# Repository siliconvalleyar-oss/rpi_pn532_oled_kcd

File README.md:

# NFC RPi Module

KiCad schematic for an NFC module combining a Raspberry Pi Zero 2W, PN532 NFC reader, and OLED display.

## Project Structure

```
nfc_rpi.kicad_sch          Root schematic
├── nfc.kicad_sch          NFC module (page 2)
│   ├── raspberry_pn532.kicad_sch   Raspberry Pi connector (page 4)
│   ├── pn532.kicad_sch             PN532 NFC controller
│   └── ...
└── ...
```

## Components

- **Raspberry Pi Zero 2W** - Main controller
- **PN532** - NFC/RFID reader/writer (SPI interface)
- **OLED Display** - Status display (I2C interface)

## Hierarchical Pin Mapping

### Raspberry Pi Sheet (J1)

| Pin | Function | Interface |
|-----|----------|-----------|
| SDA | I2C Data | OLED |
| SCL | I2C Clock | OLED |
| GPIO5 | General Purpose | - |
| GPIO6 | General Purpose | - |
| MISO | SPI Data In | PN532 |
| SCK | SPI Clock | PN532 |
| 5V | Power Supply | - |
| GND | Ground | - |

## Notes

- Hierarchical pins connect J1's GPIO pins to the parent schematic
- Global labels (SCL_OLED_RPI, SDA_OLED_RPI) handle I2C routing
- Power distribution uses hierarchical pins for 5V and GND

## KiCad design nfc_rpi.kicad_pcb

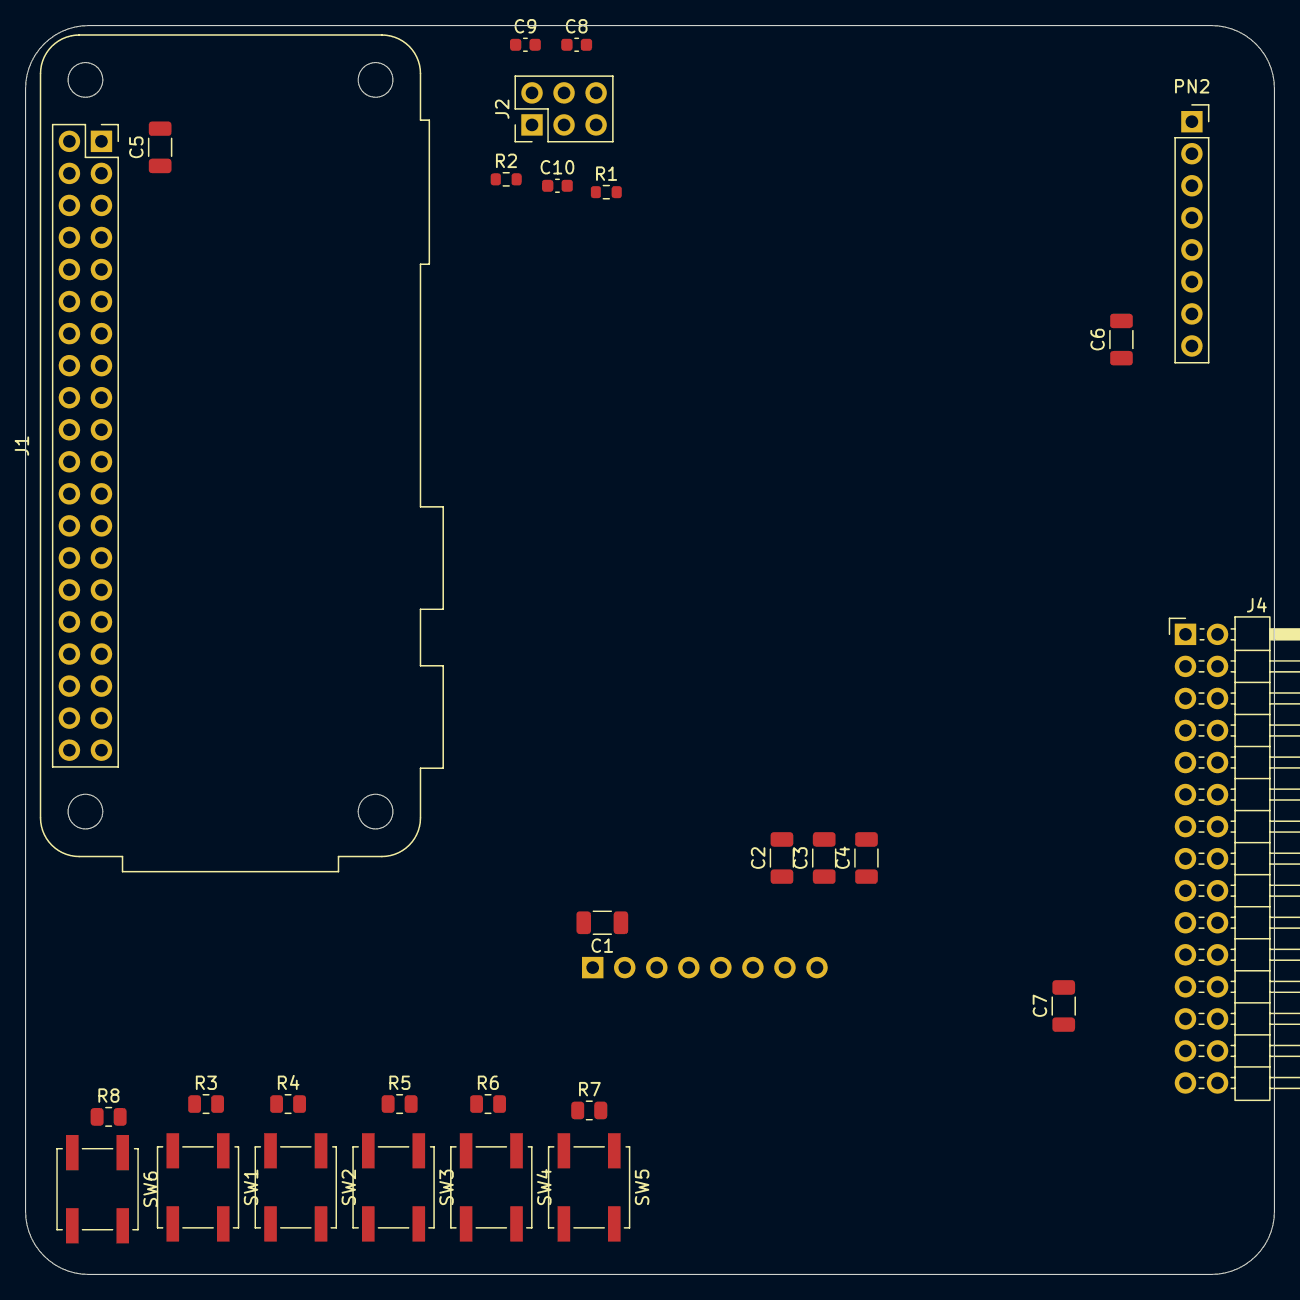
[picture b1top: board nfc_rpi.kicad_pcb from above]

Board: 2 copper layers, 99.0 x 99.0 mm, 29 parts (1 on the bottom side), 12 nets, no tracks yet.

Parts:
C1, C2, C3, C4, C5, C6, C7: 100n; C_1206_3216Metric
C8, C9, C10: 100n; C_0603_1608Metric
J1: Raspberry_Pi_zero_2w; Raspberry_Pi_Zero_Socketed_THT_FaceDown_MountingHoles
J2: OledSpiST1306; PinHeader_2x03_P2.54mm_Vertical
J3: OledSpiST7789; Adafruit_SSD1306_No_Mounting_Holes_pads
J4: Conn_02x15_Odd_Even; PinHeader_2x15_P2.54mm_Horizontal
PN2: PN532; PinSocket_1x08_P2.54mm_Vertical
R1, R2: 10K; R_0603_1608Metric
R3, R7: R_US; R_0805_2012Metric
R4, R5, R6, R8: R_0805_2012Metric
SW1, SW2, SW3, SW4, SW5, SW6: SW_Push_1P1T_NO_CK_KSC6xxJ

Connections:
+3V3: C10.1, J2.1, J3.2, R1.1, R2.1
+5V: C1.1, C2.1, C3.1, C4.1, C5.1, C6.1, C7.1, C8.1, C9.1, J1.2 (5V), J2.2, J2.4, PN2.8 (5V)
/oled/SCL_OLED: J2.5, J3.3, R1.2
/oled/SDA_OLED: J2.3, J3.4, R2.2
GND: C1.2, C2.2, C3.2, C4.2, C5.2, C6.2, C7.2, C8.2, C9.2, C10.2, J1.6 (GND), J1.9 (GND), J1.14 (GND), J1.20 (GND), J1.25 (GND), J1.30 (GND), J1.34 (GND), J1.39 (GND), J2.6, J3.1, J4.19, J4.20, J4.25, J4.26, PN2.7 (GND), SW1.1 (C), SW2.1 (C), SW3.1 (C), SW4.1 (C), SW5.1 (C), SW6.1 (C)
unnamed: J1.1 (3V3), J1.17 (3V3)
unnamed: R3.2, SW1.2 (D)
unnamed: R4.2, SW2.2 (D)
unnamed: R5.2, SW3.2 (D)
unnamed: R6.2, SW4.2 (D)
unnamed: R7.2, SW5.2 (D)
unnamed: R8.2, SW6.2 (D)
